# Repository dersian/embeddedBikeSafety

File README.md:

# embeddedBikeSafety
EBS is an Embedded solution protecting a cyclist from vehicles by detecting approaching vehicles using microphones and machine learning.

BOM is located inside the KiCad project.

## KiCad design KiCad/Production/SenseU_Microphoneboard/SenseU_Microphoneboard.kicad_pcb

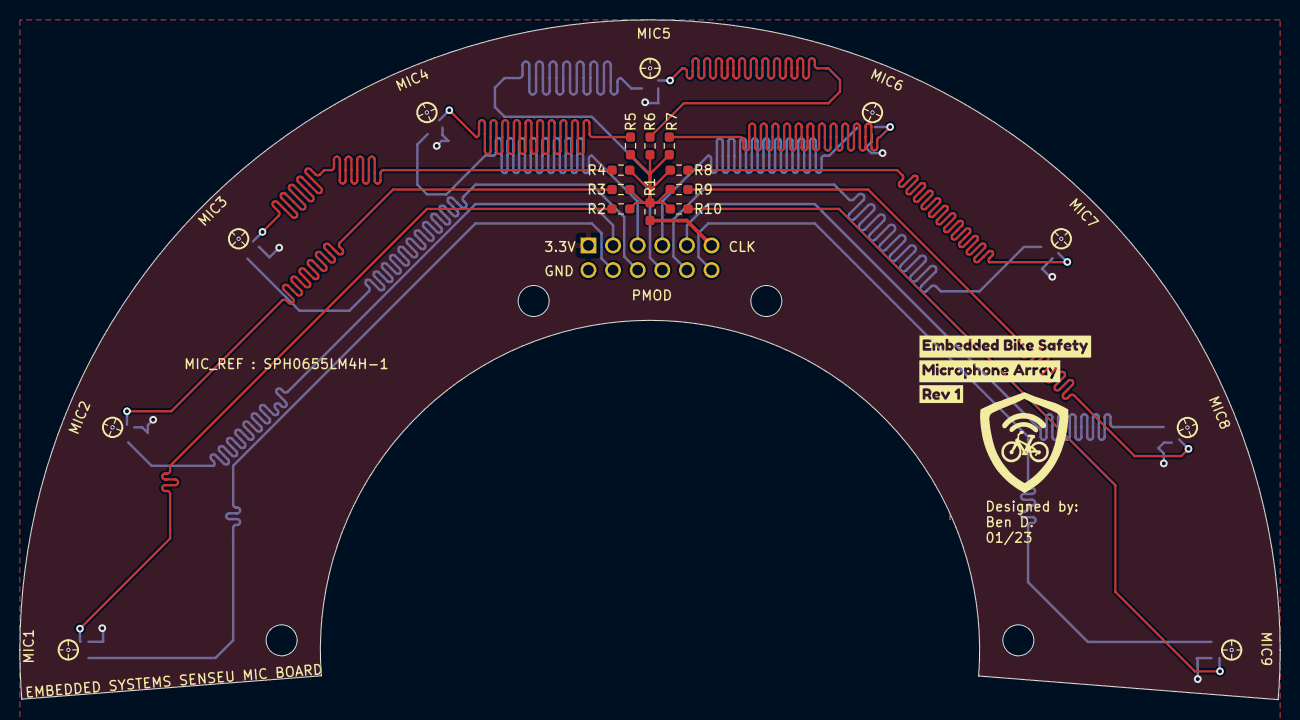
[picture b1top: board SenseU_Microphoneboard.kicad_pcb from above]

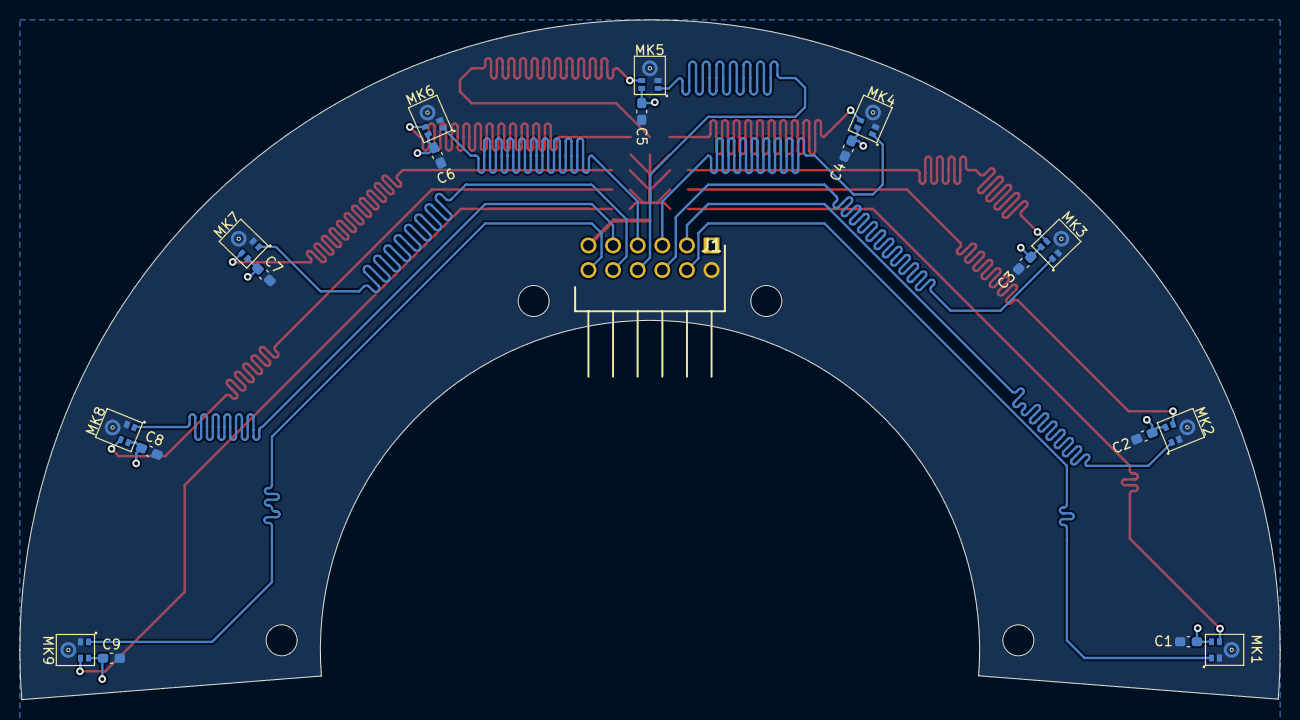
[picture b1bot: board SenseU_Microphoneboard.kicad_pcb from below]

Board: 2 copper layers, 130.0 x 70.1 mm, 32 parts (19 on the bottom side), 22 nets.

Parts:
C1, C2, C3, C4, C5, C6, C7, C8, C9: 0.1uF; C_0603_1608Metric_Pad1.08x0.95mm_HandSolder
J1: 90122-0126; 12PIN_2-ROW_RIGHT-ANGLE_90122-0126
MK1, MK2, MK3, MK4, MK5, MK6, MK7, MK8, MK9: SPH0655LM4H-1; MIC_SPH0655LM4H-1
R1: 51; R_0603_1608Metric_Pad0.98x0.95mm_HandSolder
R2, R3, R4, R5, R6, R7, R8, R9, R10: 0; R_0603_1608Metric_Pad0.98x0.95mm_HandSolder
kibuzzard-64904BCF: G***; kibuzzard-64904BCF
kibuzzard-6486612E: G***; kibuzzard-6486612E
kibuzzard-64866152: G***; kibuzzard-64866152

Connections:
3.3V: C1.1, C2.1, C3.1, C4.1, C5.1, C6.1, C7.1, C8.1, C9.1, J1.1 (VCC), MK1.5 (VDD), MK2.5 (VDD), MK3.5 (VDD), MK4.5 (VDD), MK5.5 (VDD), MK6.5 (VDD), MK7.5 (VDD), MK8.5 (VDD), MK9.5 (VDD)
CLK: R1.1, R2.1, R3.1, R4.1, R5.1, R6.1, R7.1, R8.1, R9.1, R10.1
CLK-1: MK1.4 (CLOCK), R2.2
CLK-2: MK2.4 (CLOCK), R3.2
CLK-3: MK3.4 (CLOCK), R4.2
CLK-4: MK4.4 (CLOCK), R5.2
CLK-5: MK5.4 (CLOCK), R6.2
CLK-6: MK6.4 (CLOCK), R7.2
CLK-7: MK7.4 (CLOCK), R8.2
CLK-8: MK8.4 (CLOCK), R9.2
CLK-9: MK9.4 (CLOCK), R10.2
GND: C1.2, C2.2, C3.2, C4.2, C5.2, C6.2, C7.2, C8.2, C9.2, J1.2 (GND), MK1.2 (SELECT), MK1.3 (GND), MK2.2 (SELECT), MK2.3 (GND), MK3.2 (SELECT), MK3.3 (GND), MK4.2 (SELECT), MK4.3 (GND), MK5.2 (SELECT), MK5.3 (GND), MK6.2 (SELECT), MK6.3 (GND), MK7.2 (SELECT), MK7.3 (GND), MK8.2 (SELECT), MK8.3 (GND), MK9.2 (SELECT), MK9.3 (GND)
unnamed: J1.11 (CLK), R1.2
PDM-1: J1.4 (D1), MK1.1 (DATA)
PDM-2: J1.3 (D2), MK2.1 (DATA)
PDM-3: J1.6 (D3), MK3.1 (DATA)
PDM-4: J1.5 (D4), MK4.1 (DATA)
PDM-5: J1.8 (D5), MK5.1 (DATA)
PDM-6: J1.7 (D6), MK6.1 (DATA)
PDM-7: J1.10 (D7), MK7.1 (DATA)
PDM-8: J1.9 (D8), MK8.1 (DATA)
PDM-9: J1.12 (D9), MK9.1 (DATA)

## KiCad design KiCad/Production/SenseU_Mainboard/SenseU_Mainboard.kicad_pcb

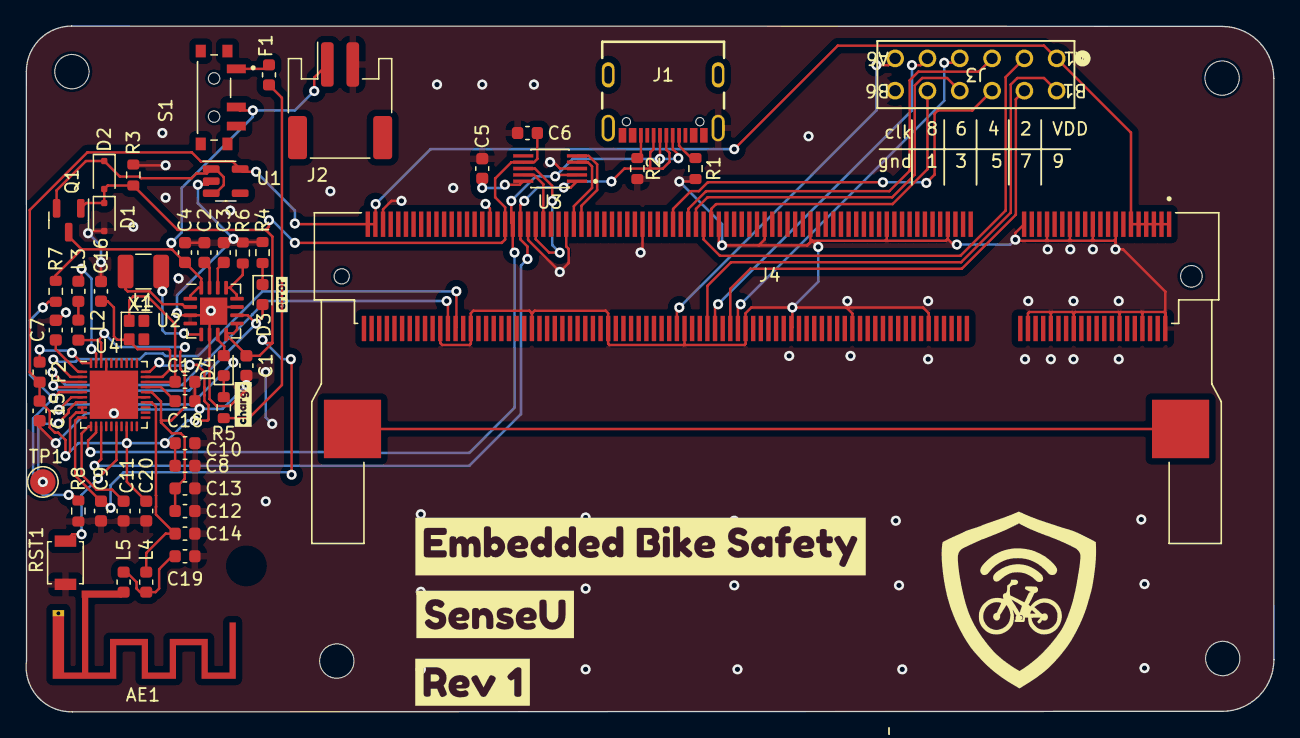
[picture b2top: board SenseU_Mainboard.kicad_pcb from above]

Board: 2 copper layers, 98.1 x 53.9 mm, 62 parts (0 on the bottom side), 53 nets.

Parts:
AE1: Antenna; Texas_SWRA117D_2.4GHz_Left
C1: 10uF; C_0603_1608Metric
C2: 0.22µ; C_0603_1608Metric
C3: 0.1µ; C_0603_1608Metric
C4: 10µ; C_0603_1608Metric
C5, C6, C7, C15, C20: 100n; C_0603_1608Metric
C8, C9, C11: 4.7µ; C_0603_1608Metric
C10, C12: 1µ; C_0603_1608Metric
C13: 47n; C_0603_1608Metric
C14: 1p ±2%; C_0603_1608Metric
C16, C17: 12p ±2%; C_0603_1608Metric
C18: 100p ±5%; C_0603_1608Metric
C19: 1.2p ±5%; C_0603_1608Metric
D1: BZT52C5V6S-7-F; D_SOD-323F
D2: 1N5819; D_SOD-323F
D3: C_Fault; LED_0603_1608Metric
D4: PLED; LED_0603_1608Metric
F1: 3A; Fuse_0603_1608Metric
F2: 04941.25NRHF; Fuse_0603_1608Metric
H1, H2, H3, H3#2: MountingHole_2.7mm_M2.5
J1: USB-C USB 2.0 MC-372; GCT_USB4105-GF-A
J2: JS2 XH 2.5; JST_PH_S2B-PH-SM4-TB_1x02-1MP_P2.00mm_Horizontal
J3: 5-534206-6; 5-534206-6_TYC
J4: 1717254-4; TE_1717254-4
L1: 1.5µ; L_1210_3225Metric
L2: 15n; L_0603_1608Metric
L3: 10µ; L_0603_1608Metric
L4: 4.7n ±5%; L_0603_1608Metric
L5: 2.2n ±5%; L_0603_1608Metric
Q1: AO3421E; SOT-23
R1, R2: 5.1K; R_0603_1608Metric
R3: 100K; R_0603_1608Metric
R4: 470; R_0603_1608Metric
R5: 1k; R_0603_1608Metric
R6: 274; R_0603_1608Metric
R7: 820K; R_0603_1608Metric
R8: 2M; R_0603_1608Metric
RST1: Jumper_2_Open; SW_SPST_B3U-1000P
S1: EG1215AA; SW_EG1215AA
TP1: TestPoint; TestPoint_Pad_D2.0mm
U1: AP2112K-3.3TRG1; SOT-23-5
U2: LTC4001EUF#TRPBF; QFN-16-1EP_4x4mm_P0.65mm_EP2.15x2.15mm
U3: COM-16278; SOP50P490X120-10N
U4: QFN-40-1EP_5x5mm_P0.4mm_EP3.8x3.8mm
X1: 32MHz ±40 ppm; Crystal_SMD_SeikoEpson_FA128-4Pin_2.0x1.6mm
kibuzzard-648E5B86: G***; kibuzzard-648E5B86
kibuzzard-648E5BB5: G***; kibuzzard-648E5BB5
kibuzzard-648E5C2D: G***; kibuzzard-648E5C2D
kibuzzard-648E5C45: G***; kibuzzard-648E5C45
kibuzzard-648E5C55: G***; kibuzzard-648E5C55

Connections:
/MCU & Comms/FPGA/CLK: J3.A6, J4.118
/MCU & Comms/FPGA/PDM-1: J3.B5, J4.109
/MCU & Comms/FPGA/PDM-2: J3.A2, J4.111
/MCU & Comms/FPGA/PDM-3: J3.B4, J4.113
/MCU & Comms/FPGA/PDM-4: J3.A3, J4.115
/MCU & Comms/FPGA/PDM-5: J3.B3, J4.119
/MCU & Comms/FPGA/PDM-6: J3.A4, J4.102
/MCU & Comms/FPGA/PDM-7: J3.B2, J4.104
/MCU & Comms/FPGA/PDM-8: J3.A5, J4.108
/MCU & Comms/FPGA/PDM-9: J3.B1, J4.110
/MCU & Comms/MicroController/IO 3: R7.2, R8.1, U4.5 (P0.05_AIN3)
/MCU & Comms/MicroController/IO 5: TP1.1, U4.7 (P0.07)
/MCU & Comms/MicroController/RF: AE1.1 (A), L5.2
/MCU & Comms/MicroController/RST: RST1.2 (B), U4.16 (P0.18/RST)
/MCU & Comms/MicroController/X1+: C16.1, U4.29 (XC2), X1.2
/MCU & Comms/MicroController/X1-: C17.1, U4.28 (XC1), X1.1
/MCU & Comms/SCL: J4.178, U4.3 (P0.01/XL2)
/MCU & Comms/SDA: J4.176, U4.2 (P0.00/XL1)
/MCU & Comms/UART_NCTS: J4.143, U3.5 (~CTS)
/MCU & Comms/UART_NRTS: J4.145, U3.4 (~RTS)
/MCU & Comms/UART_RX: J4.153, U3.9 (RXD)
/MCU & Comms/UART_TX: J4.155, U3.8 (TXD)
BATT+: C4.1, J2.1, Q1.3 (D), R7.1, S1.2, U2.1 (BAT), U2.16 (BATSENS)
CC1: J1.A5 (CC1), R1.1
CC2: J1.B5 (CC2), R2.1
Charge Fault: D3.2 (A), U2.10 (FAULT), U4.4 (P0.04_AIN2)
Charge Status: D4.2 (A), U2.7 (~CHRG), U4.6 (P0.06)
DATA+: J1.A6 (D+), J1.B6 (D+), J4.159, U3.1 (UD+), U4.13 (D+_USB)
DATA-: J1.A7 (D-), J1.B7 (D-), J4.161, U3.2 (UD-), U4.12 (D-_USB)
GND: C1.2, C2.1, C3.1, C4.2, C5.2, C6.2, C7.2, C8.2, C9.2, C10.2, C11.2, C12.2, C13.2, C14.2, C15.2, C16.2, C17.2, C18.2, C19.2, C20.2, D1.2 (A), J1.S1 (SHIELD), J2.2, J3.B6, J4.2, J4.8, J4.14, J4.15, J4.21, J4.26, J4.27, J4.32, J4.33, J4.38, J4.39, J4.47, J4.52, J4.63, J4.72, J4.83, J4.88, J4.95, J4.100, J4.107, J4.116, J4.127, J4.136, J4.147, J4.156, J4.157, J4.167, J4.172, J4.180, J4.195, R1.2, R2.2, R3.2, R4.2, R6.2, R8.2, RST1.1 (A), U1.2 (GND), U2.3 (PGND), U2.4 (GNDSENS), U2.6 (~EN), U2.11 (NTC), U2.17 (PAD), U3.3 (GND), U4.25 (VSS_PA), U4.37 (VSS), U4.41 (VSS)
unnamed: C19.1, L4.2, L5.1
unnamed: D2.1 (K), Q1.2 (S), U1.1 (VIN), U1.3 (EN)
unnamed: D3.1 (K), R4.1
unnamed: D4.1 (K), R5.1
unnamed: F1.1, S1.1
unnamed: F2.1, U4.40 (VDD)
unnamed: J4.S1 (SHIELD), J4.S2 (SHIELD)
unnamed: L2.2, L3.1
unnamed: R6.1, U2.12 (PROG), U2.13 (IDET)
unnamed: L1.2, U2.2 (SENSE)
unnamed: C3.2, U2.14 (SS)
unnamed: L1.1, U2.5 (SW)
unnamed: C2.2, U2.15 (TIMER)
unnamed: C5.1, U3.10 (V3)
unnamed: C14.1, L4.1, U4.24 (ANT_RF)
unnamed: L3.2, U4.39 (DCC)
unnamed: C7.1, U4.1 (DEC1)
unnamed: C18.1, U4.27 (DEC3)
unnamed: C12.1, C13.1, L2.1, U4.26 (DEC6), U4.38 (DEC4)
unnamed: C11.1, U4.11 (DECUSB)
VBAT: F1.2, R5.2
VBUS: C1.1, C6.1, C9.1, D1.1 (K), D2.2 (A), J4.163, Q1.1 (G), R3.1, U2.8 (PVin), U2.9 (Vinsense), U3.7 (VCC), U4.10 (VBUS)
VDD: C8.1, C10.1, C15.1, C20.1, F2.2, J3.A1, J4.1, J4.3, J4.5, J4.7, J4.9, J4.11, J4.197, J4.199, U1.5 (VOUT), U4.8 (VDD), U4.9 (VDDH), U4.18 (VDD), U4.30 (VDD)

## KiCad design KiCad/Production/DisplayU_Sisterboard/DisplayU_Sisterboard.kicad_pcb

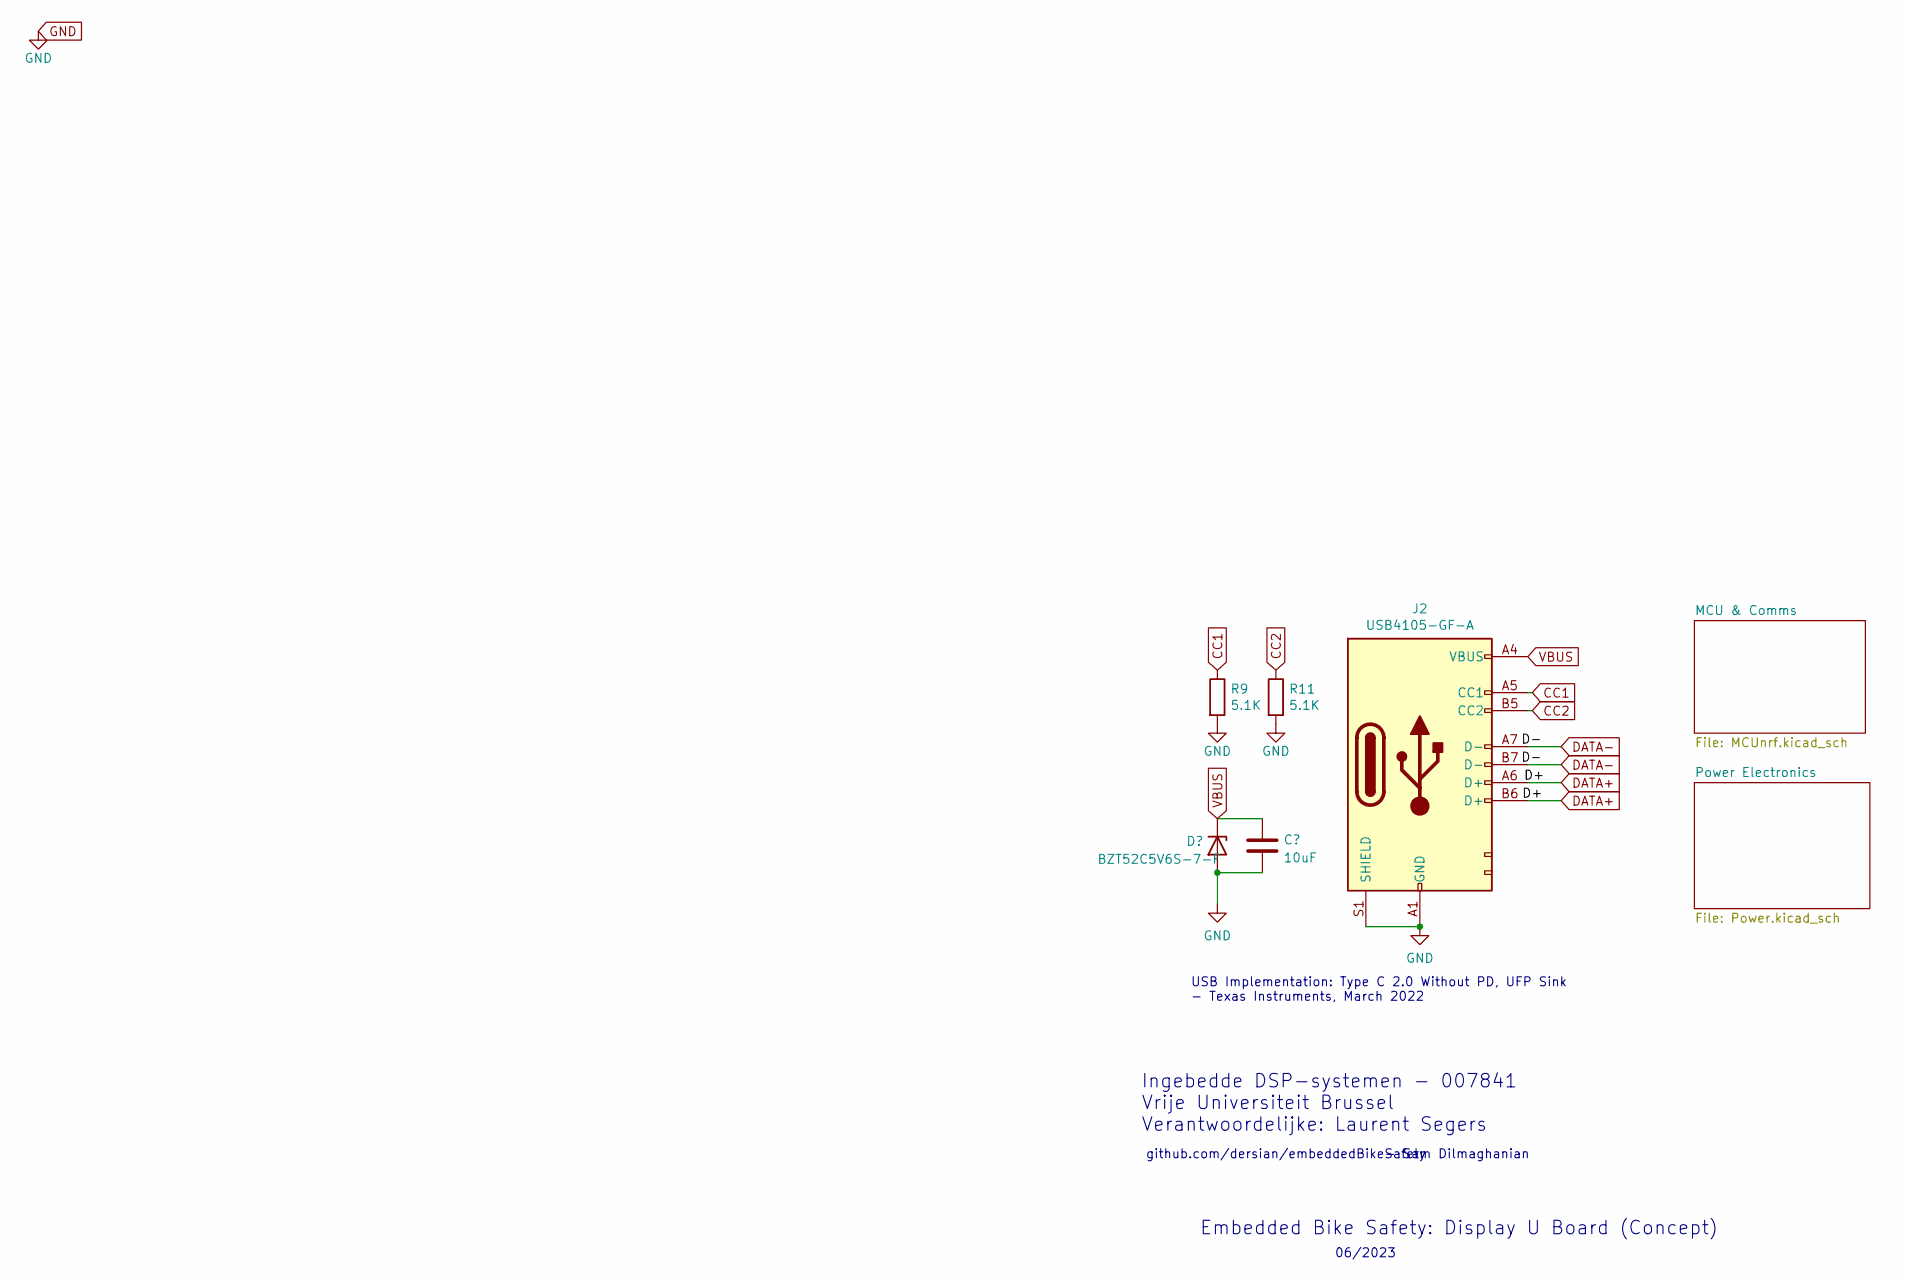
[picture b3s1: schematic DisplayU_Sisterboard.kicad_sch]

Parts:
C10: 10uF; C_0603_1608Metric_Pad1.08x0.95mm_HandSolder
D11: BZT52C5V6S-7-F; D_SOD-323F
J2: USB4105-GF-A; USB C 2.0 MC 772
R9, R11: 5.1K; R_0603_1608Metric

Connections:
CC1: J2.A5 (CC1), R9.1
CC2: J2.B5 (CC2), R11.1
DATA+: J2.A6 (D+), J2.B6 (D+); also elsewhere on the board
DATA-: J2.A7 (D-), J2.B7 (D-); also elsewhere on the board
GND: C10.2, J2.A1 (GND), J2.S1 (SHIELD), R9.2, R11.2; also elsewhere on the board
VBUS: C10.1, J2.A4 (VBUS); also elsewhere on the board

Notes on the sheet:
github.com/dersian/embeddedBikeSafety
06/2023
Embedded Bike Safety: Display U Board (Concept)
Ingebedde DSP-systemen - 007841 Vrije Universiteit Brussel Verantwoordelijke: Laurent Segers
USB Implementation: Type C 2.0 Without PD, UFP Sink - Texas Instruments, March 2022
- Sam Dilmaghanian

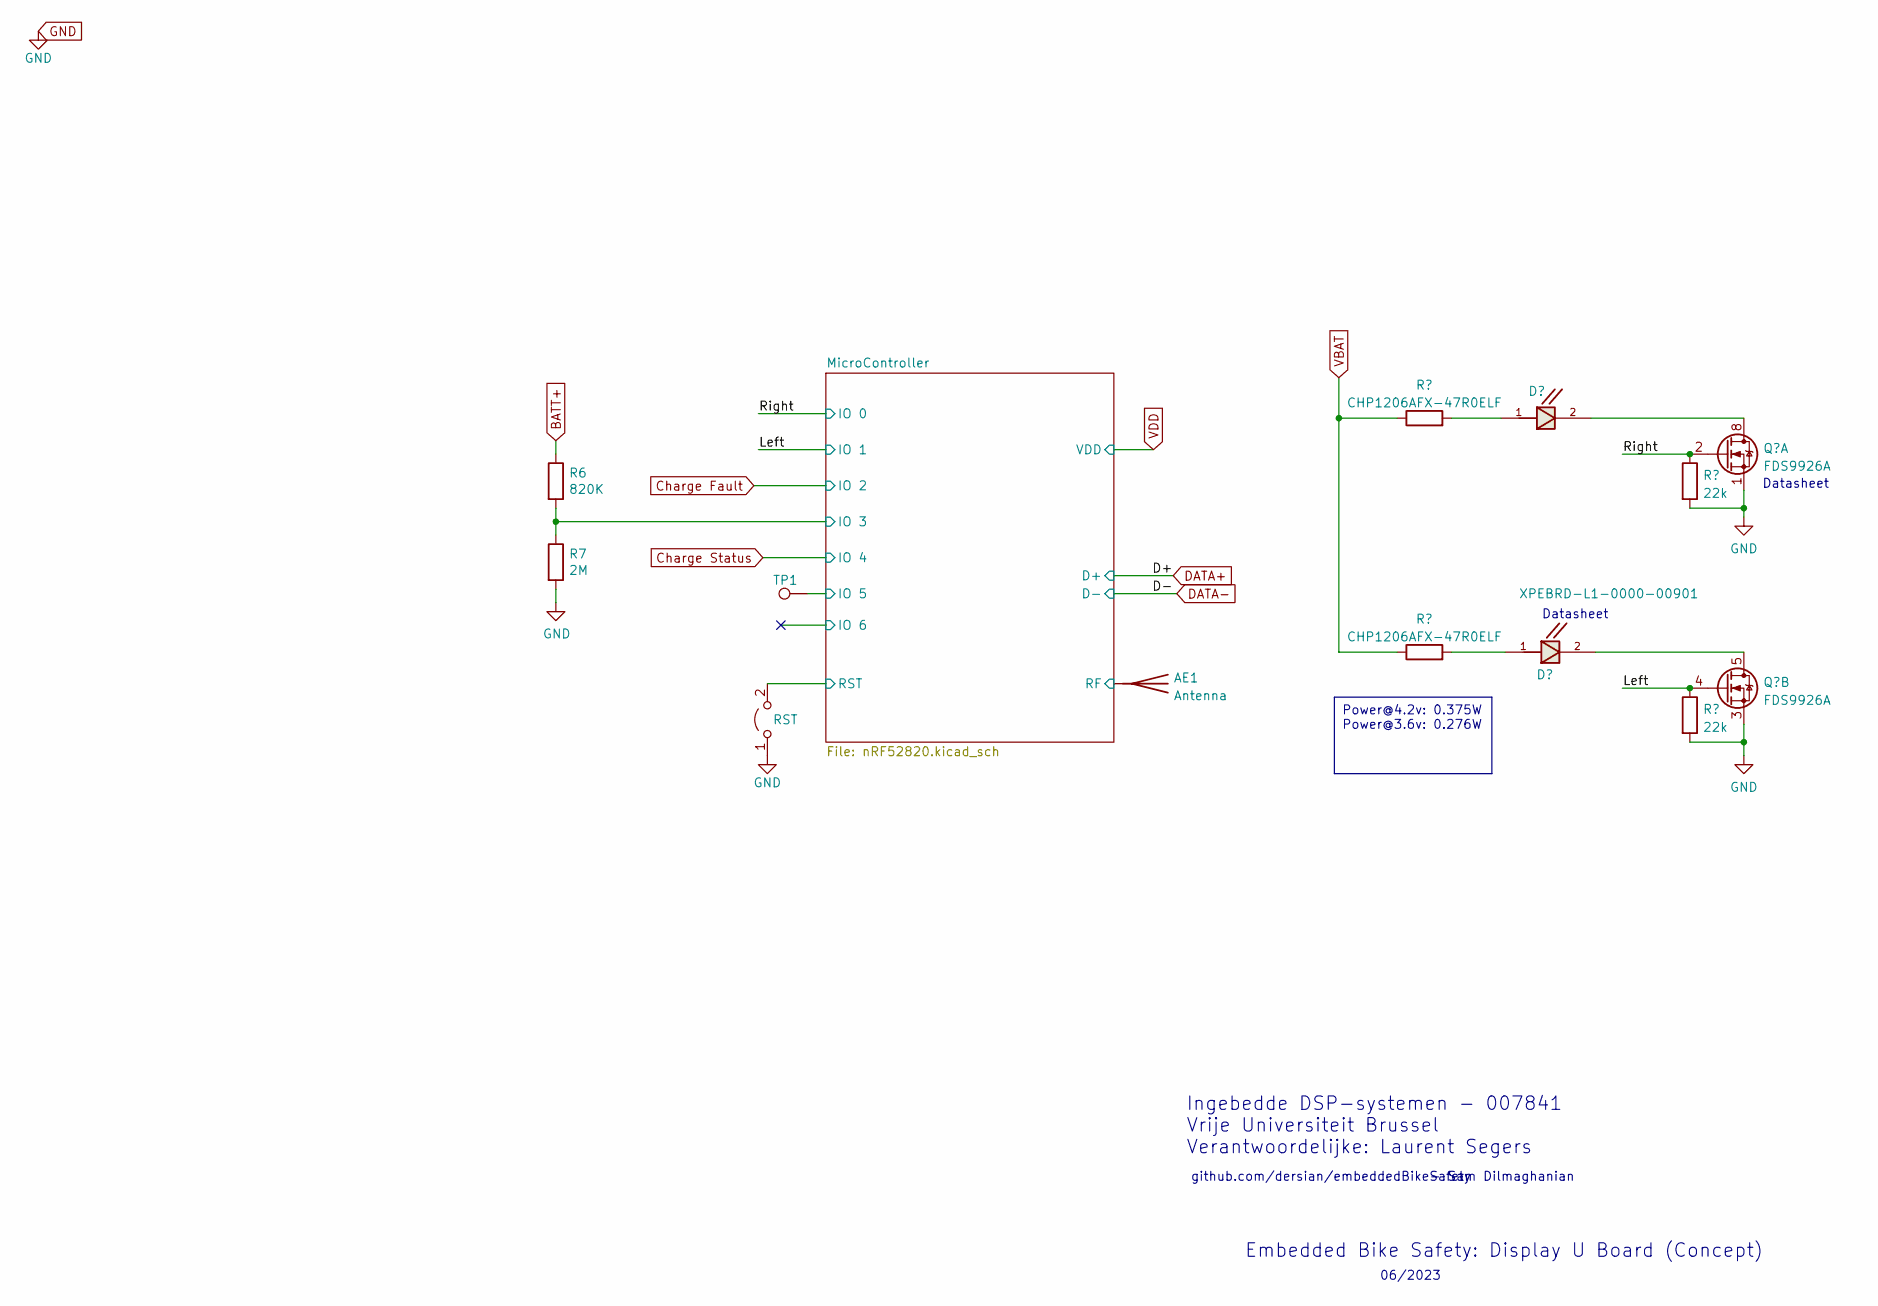
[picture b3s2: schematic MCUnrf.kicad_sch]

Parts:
AE1: Antenna; Texas_SWRA117D_2.4GHz_Left
D2, D3: XPEBRD-L1-0000-00901
Q1: FDS9926A; SOIC-8_3.9x4.9mm_P1.27mm
R2, R3: CHP1206AFX-47R0ELF; R_0603_1608Metric
R4, R5: 22k; R_0603_1608Metric
R6: 820K; R_0603_1608Metric
R7: 2M; R_0603_1608Metric
RST: Jumper_2_Open; SW_SPST_B3U-1000P
TP1: TestPoint; TestPoint_Pad_D2.0mm

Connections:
/MCU & Comms/Left: Q1.4 (G2), R5.1; also elsewhere on the board
/MCU & Comms/MicroController/IO 3: R6.2, R7.1; also elsewhere on the board
/MCU & Comms/MicroController/IO 5: TP1.1; also elsewhere on the board
/MCU & Comms/MicroController/RF: AE1.1 (A); also elsewhere on the board
/MCU & Comms/MicroController/RST: RST.2 (B); also elsewhere on the board
/MCU & Comms/Right: Q1.2 (G1), R4.1; also elsewhere on the board
BATT+: R6.1; also elsewhere on the board
GND: Q1.1 (S1), Q1.3 (S2), R4.2, R5.2, R7.2, RST.1 (A); also elsewhere on the board
unnamed: D2.1, R2.2
unnamed: D2.2, Q1.7 (D1), Q1.8 (D1)
unnamed: D3.1, R3.2
unnamed: D3.2, Q1.5 (D2), Q1.6 (D2)
VBAT: R2.1, R3.1; also elsewhere on the board

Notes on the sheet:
Power@4.2v: 0.375W Power@3.6v: 0.276W
- Sam Dilmaghanian
Ingebedde DSP-systemen - 007841 Vrije Universiteit Brussel Verantwoordelijke: Laurent Segers
06/2023
Datasheet
github.com/dersian/embeddedBikeSafety
Embedded Bike Safety: Display U Board (Concept)

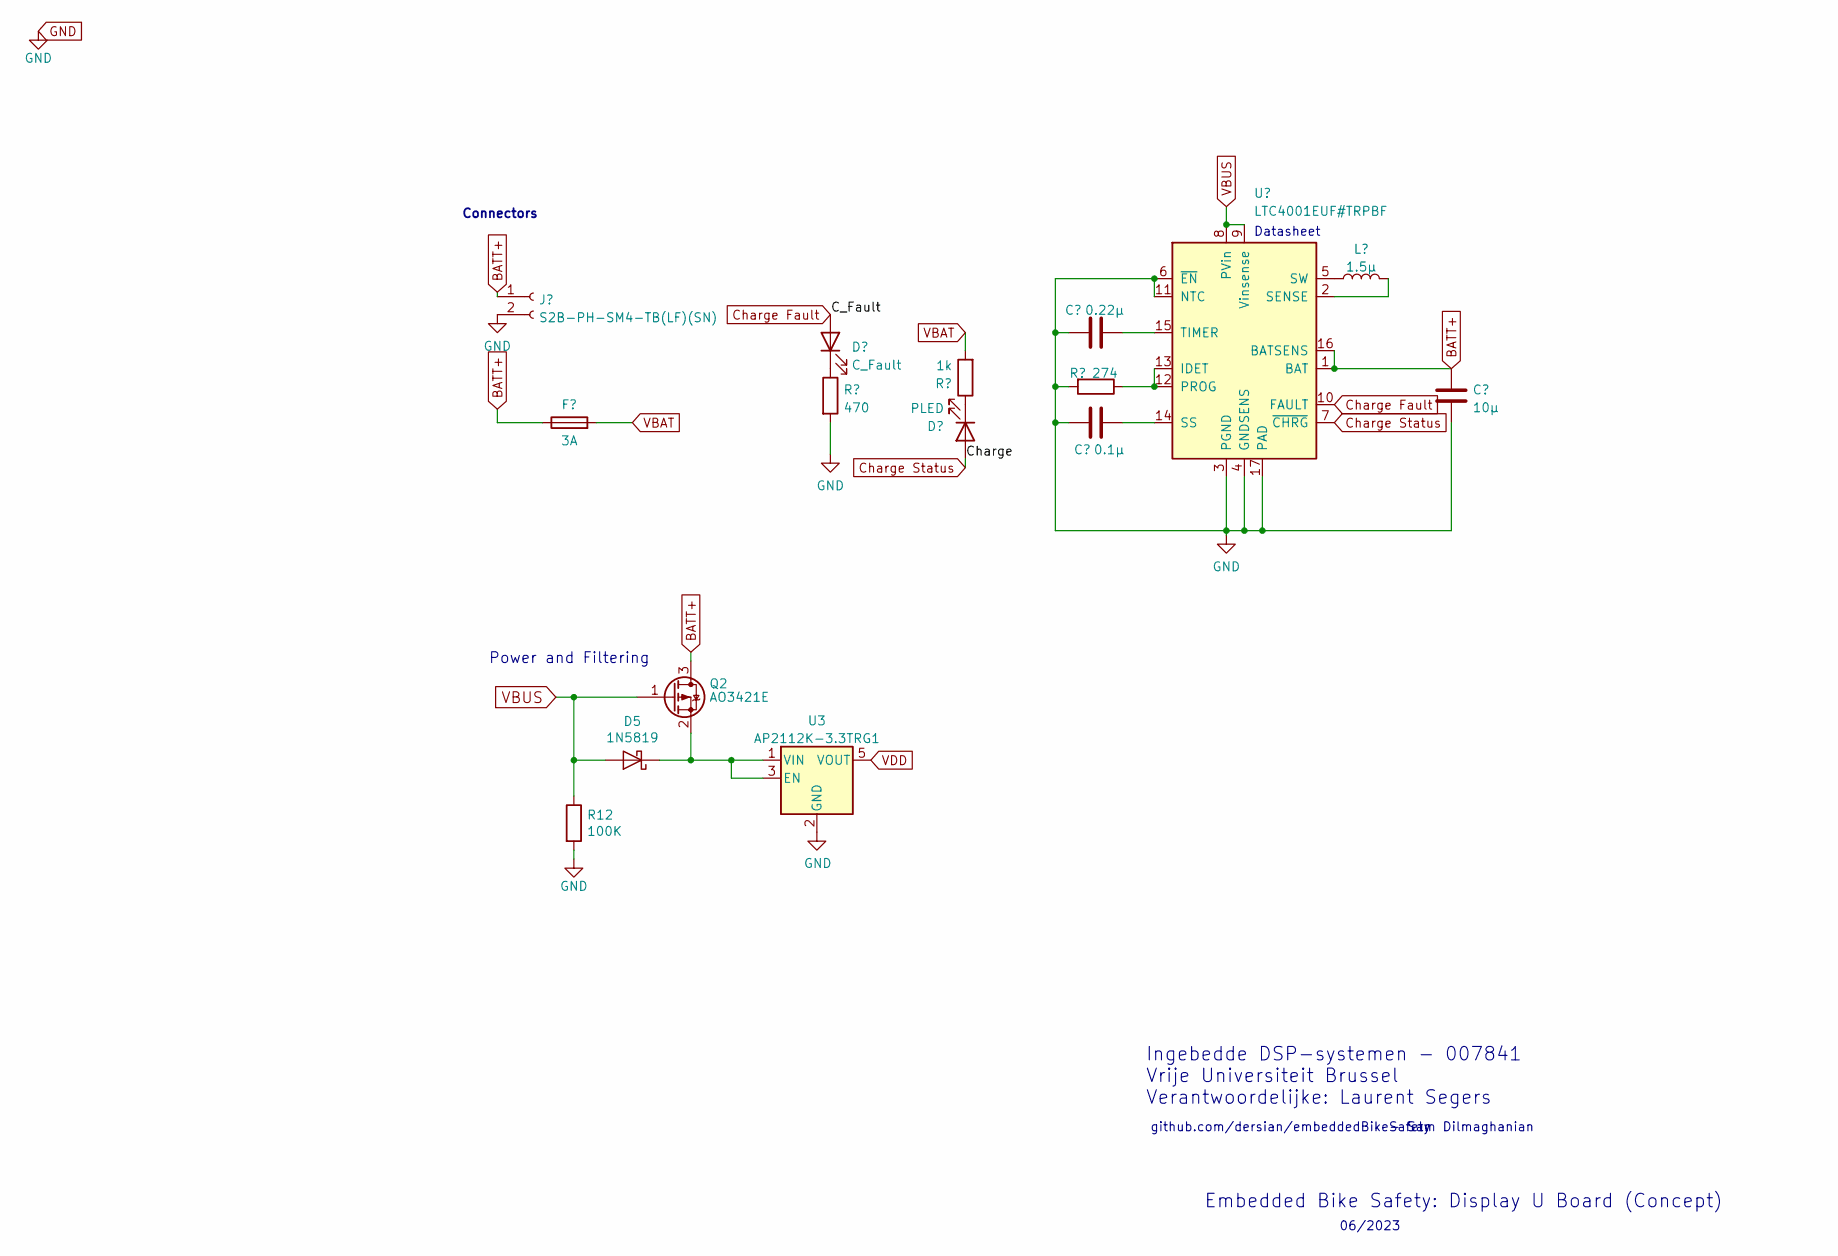
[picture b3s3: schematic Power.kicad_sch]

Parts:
C12: 0.22µ; C_0603_1608Metric_Pad1.08x0.95mm_HandSolder
C13: 0.1µ; C_0603_1608Metric_Pad1.08x0.95mm_HandSolder
C14: 10µ; C_0603_1608Metric_Pad1.08x0.95mm_HandSolder
D5: 1N5819; D_SOD-323F
D10: C_Fault; LED_0603_1608Metric
D12: PLED; LED_0603_1608Metric
F5: 3A; Fuse_0603_1608Metric
J1: S2B-PH-SM4-TB(LF)(SN); JST_PH_S2B-PH-SM4-TB_1x02-1MP_P2.00mm_Horizontal
L5: 1.5µ; L_1210_3225Metric
Q2: AO3421E; SOT-23
R10: 470; R_0603_1608Metric
R12: 100K; R_0603_1608Metric
R13: 1k; R_0603_1608Metric
R14: 274; R_0603_1608Metric
U3: AP2112K-3.3TRG1; SOT-23-5
U4: LTC4001EUF#TRPBF; QFN-16-1EP_4x4mm_P0.65mm_EP2.15x2.15mm; MPN LTC4001EUF#TRPBF

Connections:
BATT+: C14.1, F5.1, J1.1, Q2.3 (D), U4.1 (BAT), U4.16 (BATSENS); also elsewhere on the board
Charge Fault: D10.2 (A), U4.10 (FAULT); also elsewhere on the board
Charge Status: D12.2 (A), U4.7 (~CHRG); also elsewhere on the board
GND: C12.1, C13.1, C14.2, J1.2, R10.2, R12.2, R14.2, U3.2 (GND), U4.3 (PGND), U4.4 (GNDSENS), U4.6 (~EN), U4.11 (NTC), U4.17 (PAD); also elsewhere on the board
unnamed: D5.1 (K), Q2.2 (S), U3.1 (VIN), U3.3 (EN)
unnamed: D10.1 (K), R10.1
unnamed: D12.1 (K), R13.1
unnamed: R14.1, U4.12 (PROG), U4.13 (IDET)
unnamed: L5.2, U4.2 (SENSE)
unnamed: C13.2, U4.14 (SS)
unnamed: L5.1, U4.5 (SW)
unnamed: C12.2, U4.15 (TIMER)
VBAT: F5.2, R13.2; also elsewhere on the board
VBUS: D5.2 (A), Q2.1 (G), R12.1, U4.8 (PVin), U4.9 (Vinsense); also elsewhere on the board
VDD: U3.5 (VOUT); also elsewhere on the board

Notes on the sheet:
06/2023
Power and Filtering
github.com/dersian/embeddedBikeSafety
Connectors
- Sam Dilmaghanian
Embedded Bike Safety: Display U Board (Concept)
Ingebedde DSP-systemen - 007841 Vrije Universiteit Brussel Verantwoordelijke: Laurent Segers
Datasheet

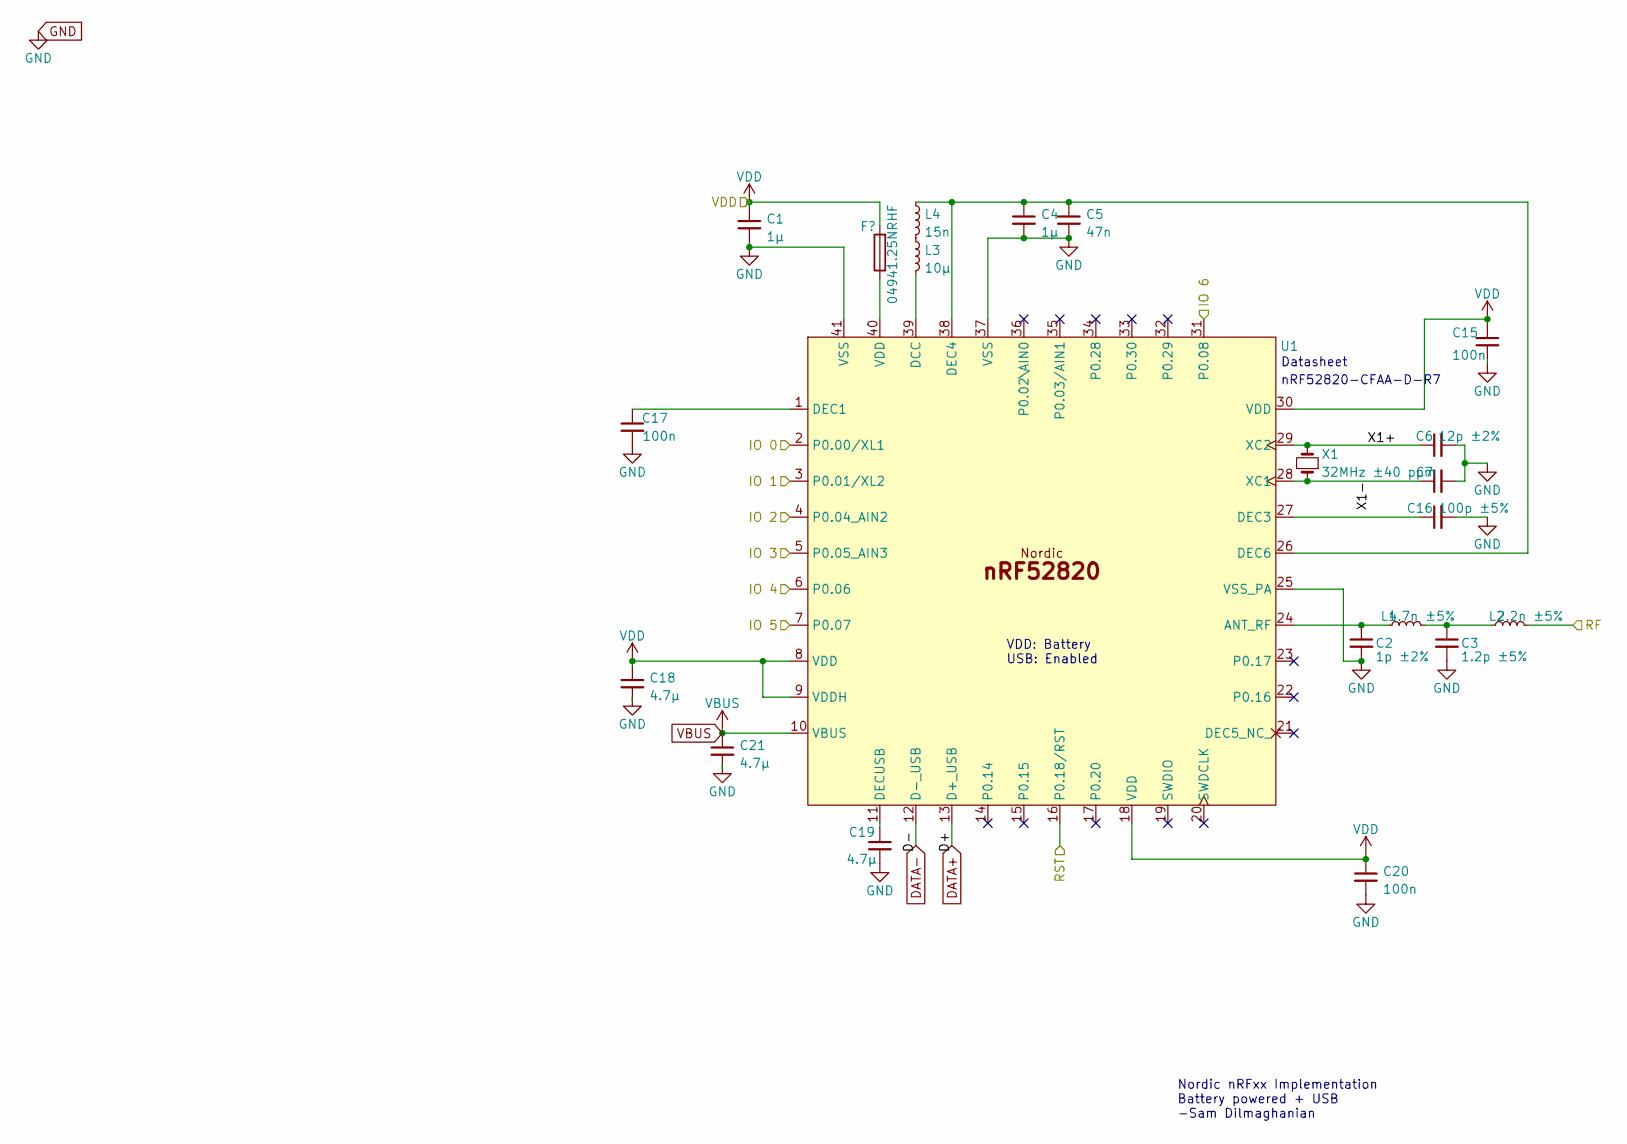
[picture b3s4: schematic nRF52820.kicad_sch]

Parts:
C1, C4: 1µ; C_0603_1608Metric
C2: 1p ±2%; C_0603_1608Metric
C3: 1.2p ±5%; C_0603_1608Metric
C5: 47n; C_0603_1608Metric
C6, C7: 12p ±2%; C_0603_1608Metric
C15, C17, C20: 100n; C_0603_1608Metric
C16: 100p ±5%; C_0603_1608Metric
C18, C19, C21: 4.7µ; C_0603_1608Metric
F4: 04941.25NRHF; Fuse_0603_1608Metric
L1: 4.7n ±5%; L_0603_1608Metric
L2: 2.2n ±5%; L_0603_1608Metric
L3: 10µ; L_0603_1608Metric
L4: 15n; L_0603_1608Metric
U1: QFN-40-1EP_5x5mm_P0.4mm_EP3.8x3.8mm
X1: 32MHz ±40 ppm; Crystal_SMD_SeikoEpson_FA128-4Pin_2.0x1.6mm

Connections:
/MCU & Comms/Left: U1.3 (P0.01/XL2); also elsewhere on the board
/MCU & Comms/MicroController/IO 3: U1.5 (P0.05_AIN3); also elsewhere on the board
/MCU & Comms/MicroController/IO 5: U1.7 (P0.07); also elsewhere on the board
/MCU & Comms/MicroController/RF: L2.2; also elsewhere on the board
/MCU & Comms/MicroController/RST: U1.16 (P0.18/RST); also elsewhere on the board
/MCU & Comms/MicroController/X1+: C6.1, U1.29 (XC2), X1.2, X1.3
/MCU & Comms/MicroController/X1-: C7.1, U1.28 (XC1), X1.1, X1.4
/MCU & Comms/Right: U1.2 (P0.00/XL1); also elsewhere on the board
Charge Fault: U1.4 (P0.04_AIN2); also elsewhere on the board
Charge Status: U1.6 (P0.06); also elsewhere on the board
DATA+: U1.13 (D+_USB); also elsewhere on the board
DATA-: U1.12 (D-_USB); also elsewhere on the board
GND: C1.2, C2.2, C3.2, C4.2, C5.2, C6.2, C7.2, C15.2, C16.2, C17.2, C18.2, C19.2, C20.2, C21.2, U1.25 (VSS_PA), U1.37 (VSS), U1.41 (VSS); also elsewhere on the board
unnamed: C3.1, L1.2, L2.1
unnamed 24: U1.40 (VDD); also elsewhere on the board
unnamed: L3.1, L4.2
unnamed: C2.1, L1.1, U1.24 (ANT_RF)
unnamed: L3.2, U1.39 (DCC)
unnamed: C17.1, U1.1 (DEC1)
unnamed: C16.1, U1.27 (DEC3)
unnamed: C4.1, C5.1, L4.1, U1.26 (DEC6), U1.38 (DEC4)
unnamed: C19.1, U1.11 (DECUSB)
VBUS: C21.1, U1.10 (VBUS); also elsewhere on the board
VDD: C1.1, C15.1, C18.1, C20.1, U1.8 (VDD), U1.9 (VDDH), U1.18 (VDD), U1.30 (VDD); also elsewhere on the board

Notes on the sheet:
Nordic nRFxx Implementation Battery powered + USB -Sam Dilmaghanian
nRF52820-CFAA-D-R7
Datasheet
VDD: Battery USB: Enabled

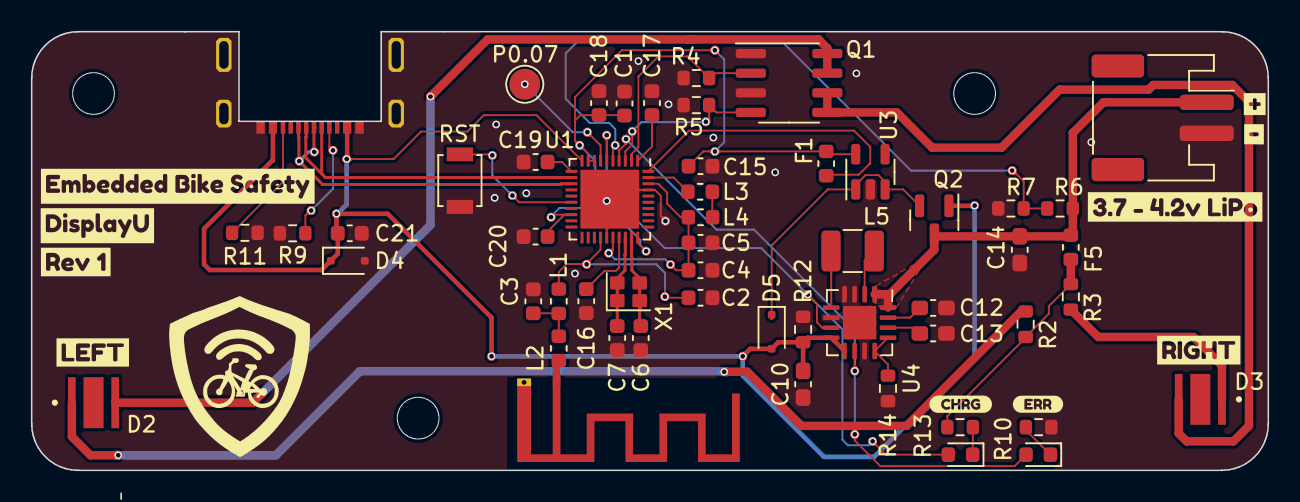
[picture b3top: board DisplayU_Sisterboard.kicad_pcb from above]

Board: 2 copper layers, 80.0 x 28.4 mm, 64 parts (0 on the bottom side), 40 nets.

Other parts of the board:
D4: BZT52C5V6S-7-F; D_SOD-323F
F1: 04941.25NRHF; Fuse_0603_1608Metric
kibuzzard-648A3F17: G***; kibuzzard-648A3F17
kibuzzard-648A3F39: G***; kibuzzard-648A3F39
kibuzzard-648A3F78: G***; kibuzzard-648A3F78
kibuzzard-64865EC8: G***; kibuzzard-64865EC8
kibuzzard-64865EDB: G***; kibuzzard-64865EDB
kibuzzard-64865F2D: G***; kibuzzard-64865F2D
kibuzzard-64865F18: G***; kibuzzard-64865F18
kibuzzard-6486612E: G***; kibuzzard-6486612E
kibuzzard-64866148: G***; kibuzzard-64866148
kibuzzard-64866152: G***; kibuzzard-64866152

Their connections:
GND: D4.2 (A); also elsewhere on the board
unnamed 24: F1.1; also elsewhere on the board
VBUS: D4.1 (K); also elsewhere on the board
VDD: F1.2; also elsewhere on the board

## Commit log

2022-12-06 Init
2022-12-06 Structure
2022-12-06 Implemented basic battery circuit
2022-12-06 Clarified BOM Location
2023-03-30 hello
2023-04-04 TS2CAN TODO
2023-04-10 EBS_Main init
2023-04-10 close
2023-04-11 Pres
2023-04-12 schematics of SenseU microphoneboard
2023-04-20 PCB design V1 without routing or component placement
2023-04-24 PCB V1 finished (9 MEMS), DRC violation rules pending
2023-04-25 Changed MEMS pad diameter from 0.6mm to 0.8mm, DRC violations still pending
2023-05-10 drill holes added + mic footprint changed to comply to DRC errors
2023-05-11 Changed board constraints to eurocircuit standard + silkscreen
2023-05-12 DaS + Filters
2023-05-12 Final version of PCB
2023-05-22 fixing merge issues
2023-05-22 removed the local microphoneboard on main branch
2023-05-22 Added the correct version of the microphone board on main
2023-06-04 Add files via upload
    Filters done, but Beamforming can probably better.
2023-06-07 found the fpga footprint and added it on schematic
2023-06-08 added gnd, I2C, USB signals
2023-06-08 UART
2023-06-10 Started Displayboard Journey
    Many adventures to come!
2023-06-10 Microcontroller Choice
    Nordic nRF52820
2023-06-10 Microcontroller integration (almost done)
2023-06-10 Display U is like 99% finished
    - BMS Chips prob not needed
    - LDO Chip prob not needed
    - Final touches
    > Start on routing
2023-06-11 Schematic is done
2023-06-12 Routing
2023-06-12 Fixes
2023-06-12 overgenomen stuff put in sense u main
2023-06-12 added fpga pins
2023-06-12 added a lot
2023-06-12 added gnd label
2023-06-12 Berekening/Metingen Verslag
2023-06-13 Add files via upload
    sources0609 did simulate and compile but take more than 200% of the available LUTs
    sources0613 tries to utilize a lot less LUTs but I have not been able to make it work yet.
    ExtraFilesForSimulation has files that need to be copied to name.sim/sim_1/behav/xsim
2023-06-15 Documentation&3DCAD
2023-06-15 Added PDM Microphone Read VHDL Code
2023-06-17 added USB TO UART
2023-06-17 removed batt co to fpga and added switch
2023-06-17 assigning components
2023-06-17 changed place of usb to uart
2023-06-18 routing SenseU done
2023-06-19 Logo EBS
2023-06-19 Logo's
2023-06-20 added gerber
2023-06-20 really did this time
2023-06-20 Added Matlab simulations & other files
2023-06-21 Finished Report
2023-06-21 more vhdl
